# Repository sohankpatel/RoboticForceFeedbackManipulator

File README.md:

# RoboticForceFeedbackManipulator
Final Project for ECE 445, Manipulator with user force-feedback

This is a project I did for my Senior Design class

It is a Robotic manipulator and glove system meant to allow the wearer to "feel" forces from the robotic hand

Details are contained in the Final Paper

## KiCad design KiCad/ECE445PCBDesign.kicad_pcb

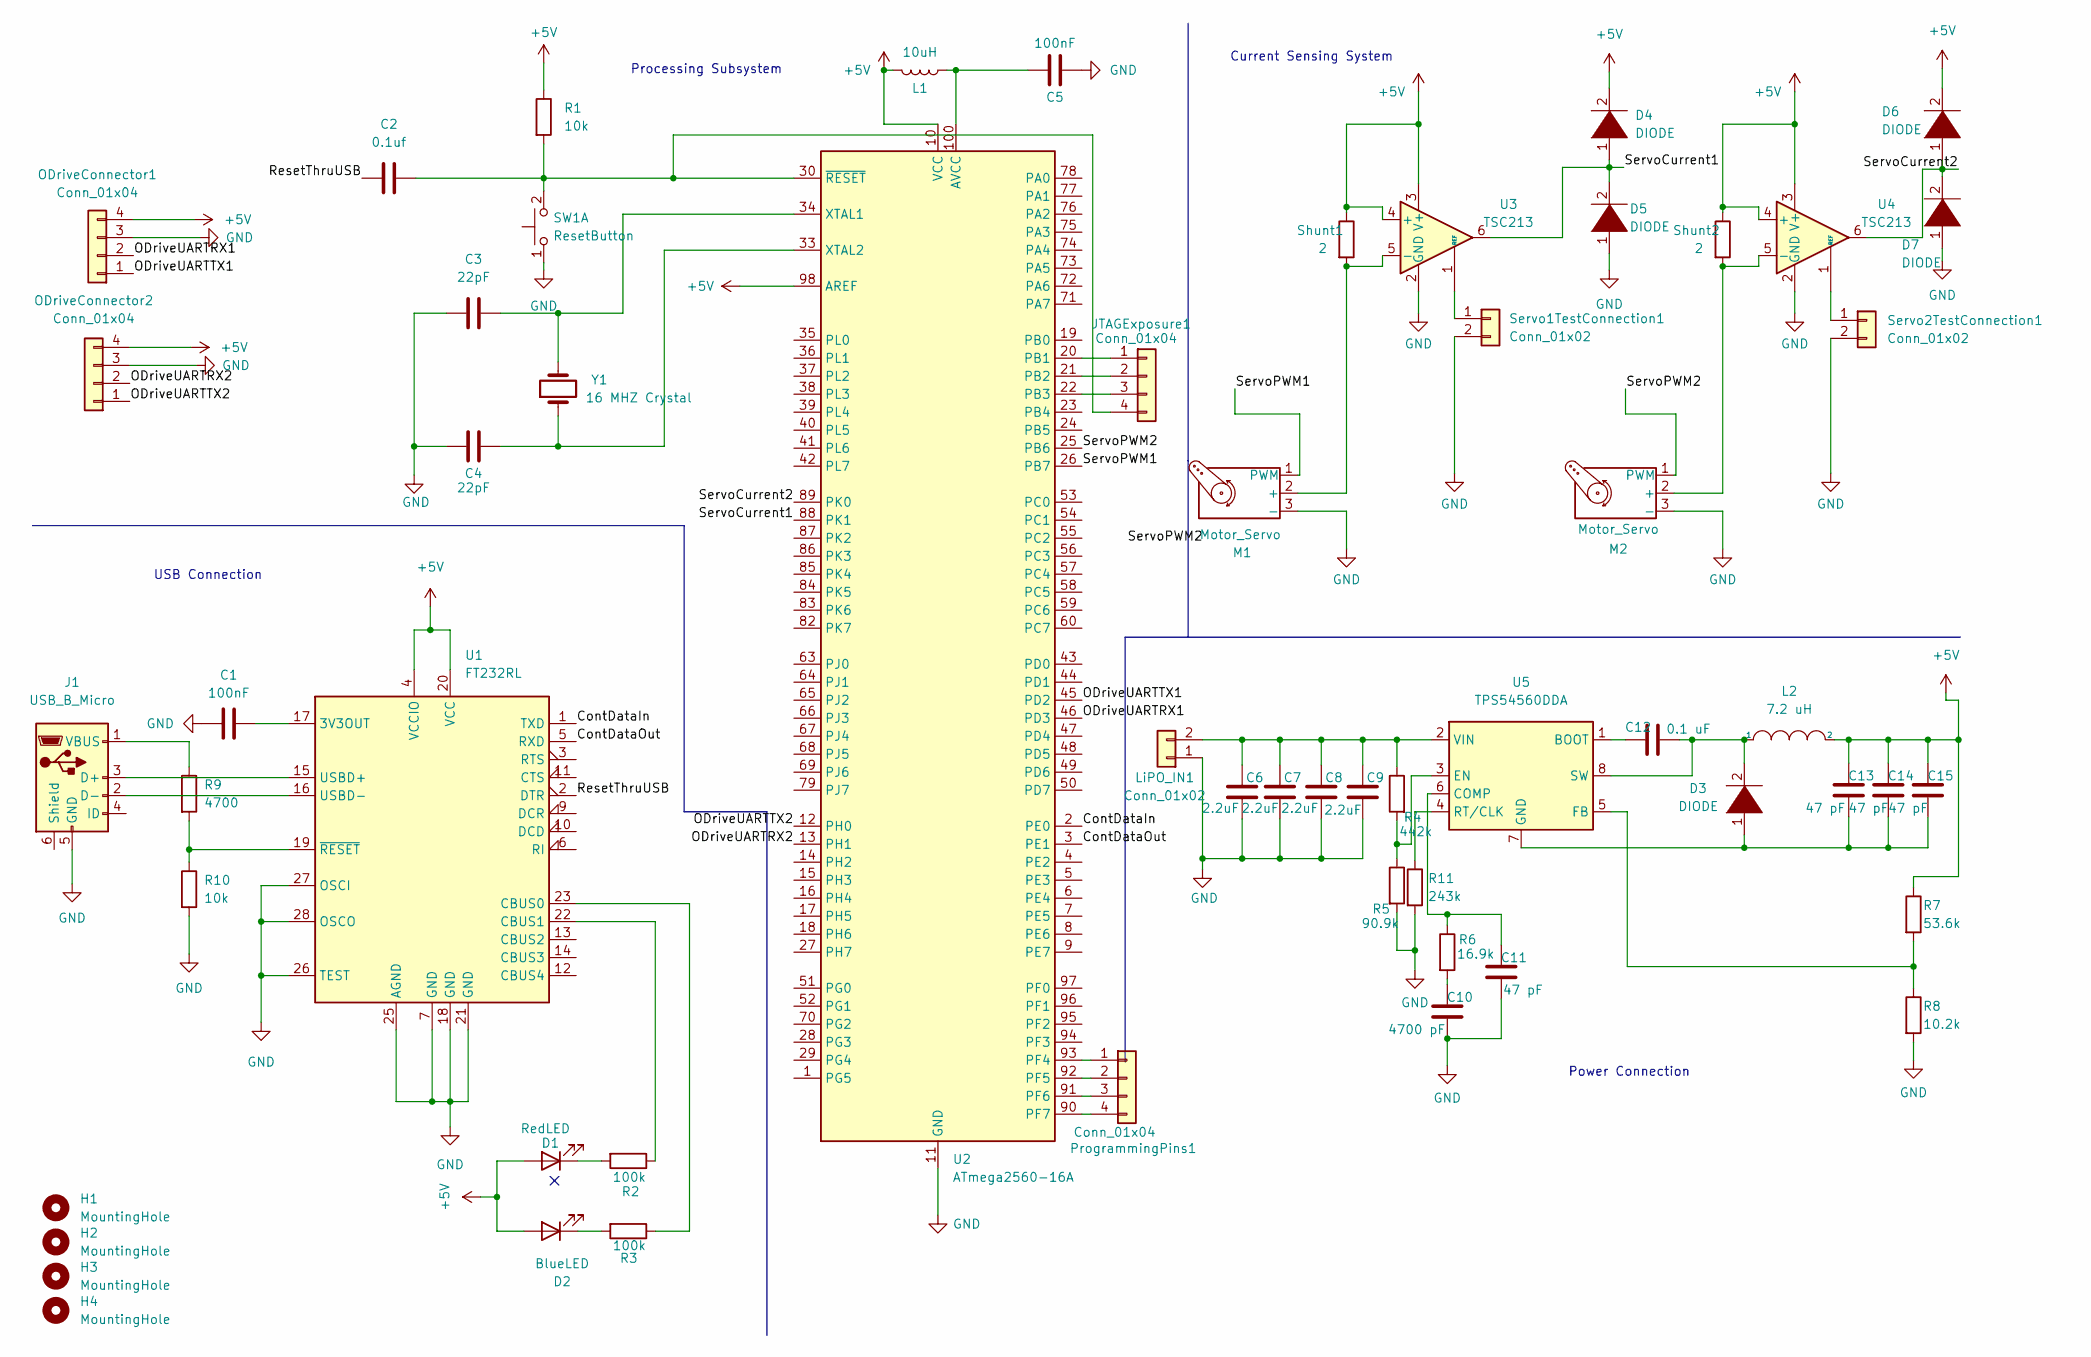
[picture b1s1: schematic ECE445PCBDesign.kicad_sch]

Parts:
C1, C5: 100nF; C_0805_2012Metric_Pad1.18x1.45mm_HandSolder
C2: 0.1uf; C_0805_2012Metric_Pad1.18x1.45mm_HandSolder
C3, C4: 22pF; C_0805_2012Metric_Pad1.18x1.45mm_HandSolder
C6, C7, C8, C9: 2.2uF; C_0805_2012Metric_Pad1.18x1.45mm_HandSolder
C10: 4700 pF; C_0805_2012Metric_Pad1.18x1.45mm_HandSolder
C11, C13, C14, C15: 47 pF; C_0805_2012Metric_Pad1.18x1.45mm_HandSolder
C12: 0.1 uF; C_0805_2012Metric_Pad1.18x1.45mm_HandSolder
D1: RedLED; D_0603_1608Metric_Pad1.05x0.95mm_HandSolder
D2: BlueLED; D_0603_1608Metric_Pad1.05x0.95mm_HandSolder
D3, D4, D5, D6, D7: DIODE; Vishay-B360A-E3_61T-0-0-0
H1, H2, H3, H4: MountingHole; MountingHole_3.2mm_M3
J1: USB_B_Micro; USB_Mini-B_AdamTech_MUSB-B5-S-VT-TSMT-1_SMD_Vertical
JTAGExposure1: Conn_01x04; Molex_KK-254_AE-6410-04A_1x04_P2.54mm_Vertical
L1: 10uH; L_0603_1608Metric_Pad1.05x0.95mm_HandSolder
L2: 7.2 uH; WE-PDF59
LiPO_IN1: Conn_01x02; SolderWire-2sqmm_1x02_P7.8mm_D2mm_OD3.9mm
M1, M2: Motor_Servo; Molex_KK-254_AE-6410-03A_1x03_P2.54mm_Vertical
ODriveConnector1, ODriveConnector2: Conn_01x04; Molex_KK-254_AE-6410-04A_1x04_P2.54mm_Vertical
ProgrammingPins1: Conn_01x04; Molex_KK-254_AE-6410-04A_1x04_P2.54mm_Vertical
R1, R10: 10k; R_0805_2012Metric_Pad1.20x1.40mm_HandSolder
R2, R3: 100k; R_0805_2012Metric_Pad1.20x1.40mm_HandSolder
R4: 442k; R_0805_2012Metric_Pad1.20x1.40mm_HandSolder
R5: 90.9k; R_0805_2012Metric_Pad1.20x1.40mm_HandSolder
R6: 16.9k; R_0805_2012Metric_Pad1.20x1.40mm_HandSolder
R7: 53.6k; R_0805_2012Metric_Pad1.20x1.40mm_HandSolder
R8: 10.2k; R_0805_2012Metric_Pad1.20x1.40mm_HandSolder
R9: 4700; R_0805_2012Metric_Pad1.20x1.40mm_HandSolder
R11: 243k; R_0805_2012Metric_Pad1.20x1.40mm_HandSolder
SW1: ResetButton; SW_Push_1P1T_NO_6x6mm_H9.5mm
Servo1TestConnection1, Servo2TestConnection1: Conn_01x02; Molex_KK-254_AE-6410-02A_1x02_P2.54mm_Vertical
Shunt1, Shunt2: 2; R_0805_2012Metric_Pad1.20x1.40mm_HandSolder
U1: FT232RL; SSOP-28_5.3x10.2mm_P0.65mm
U2: ATmega2560-16A; TQFP-100_14x14mm_P0.5mm
U3, U4: TSC213; TSC213ICT
U5: TPS54560DDA; Texas_R-PDSO-G8_EP2.95x4.9mm_Mask2.4x3.1mm_ThermalVias
Y1: 16 MHZ Crystal; 830058383B

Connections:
+5V: C13.2, C14.2, C15.2, D1.2 (A), D2.2 (A), D4.2 (A), D6.2 (A), L1.2, L2.2, ODriveConnector1.4, ODriveConnector2.4, R1.1, R7.1, Shunt1.1, Shunt2.1, U1.4 (VCCIO), U1.20 (VCC), U2.10 (VCC), U2.31 (VCC), U2.61 (VCC), U2.80 (VCC), U2.98 (AREF), U3.3 (V+), U3.4 (+), U4.3 (V+), U4.4 (+)
/ContDataIn: U1.1 (TXD), U2.2 (PE0)
/ContDataOut: U1.5 (RXD), U2.3 (PE1)
/ODriveUARTRX1: ODriveConnector1.2, U2.46 (PD3)
/ODriveUARTRX2: ODriveConnector2.2, U2.13 (PH1)
/ODriveUARTTX1: ODriveConnector1.1, U2.45 (PD2)
/ODriveUARTTX2: ODriveConnector2.1, U2.12 (PH0)
/ResetThruUSB: C2.1, U1.2 (DTR)
/ServoCurrent1: D4.1 (K), D5.2 (A), U2.88 (PK1), U3.6
/ServoCurrent2: D6.1 (K), D7.2 (A), U2.89 (PK0), U4.6
/ServoPWM1: M1.1 (PWM), U2.26 (PB7)
/ServoPWM2: M2.1 (PWM), U2.25 (PB6)
GND: C1.1, C3.1, C4.1, C5.2, C6.1, C7.1, C8.1, C9.1, C10.1, C11.1, D5.1 (K), D7.1 (K), J1.5 (GND), LiPO_IN1.1, M1.3 (-), M2.3 (-), ODriveConnector1.3, ODriveConnector2.3, R5.2, R8.2, R10.2, R11.2, SW1.1 (C), Servo1TestConnection1.2, Servo2TestConnection1.2, U1.7 (GND), U1.18 (GND), U1.21 (GND), U1.25 (AGND), U1.26 (TEST), U1.27 (OSCI), U1.28 (OSCO), U2.11 (GND), U2.32 (GND), U2.62 (GND), U2.81 (GND), U2.99 (GND), U3.2 (GND), U4.2 (GND)
unnamed: C1.2, U1.17 (3V3OUT)
unnamed: C2.2, JTAGExposure1.4, R1.2, SW1.2 (D), U2.30 (~RESET)
unnamed: C3.2, U2.34 (XTAL1), Y1.2
unnamed: C4.2, U2.33 (XTAL2), Y1.1
unnamed: C5.1, L1.1, U2.100 (AVCC)
unnamed: C6.2, C7.2, C8.2, C9.2, LiPO_IN1.2, R4.1, U5.2 (VIN)
unnamed: C10.2, R6.2
unnamed: C11.2, R6.1, U5.6 (COMP)
unnamed: C12.1, D3.2 (A), L2.1, U5.8 (SW)
unnamed: C12.2, U5.1 (BOOT)
unnamed: C13.1, C14.1, C15.1, D3.1 (K), U5.7 (GND), U5.9 (GND)
unnamed: D1.1 (K), R2.2
unnamed: D2.1 (K), R3.2
unnamed: M1.2 (+), Shunt1.2, U3.5 (-)
unnamed: M2.2 (+), Shunt2.2, U4.5 (-)
unnamed: R2.1, U1.22 (CBUS1)
unnamed: R3.1, U1.23 (CBUS0)
unnamed: R4.2, R5.1, U5.3 (EN)
unnamed: R7.2, R8.1, U5.5 (FB)
unnamed: J1.1 (VBUS), R9.1
unnamed: Servo1TestConnection1.1, U3.1 (REF)
unnamed: Servo2TestConnection1.1, U4.1 (REF)
unnamed: J1.3 (D+), U1.15 (USBD+)
unnamed: J1.2 (D-), U1.16 (USBD-)
unnamed: R9.2, R10.1, U1.19 (~RESET)
unnamed: JTAGExposure1.1, U2.20 (PB1)
unnamed: JTAGExposure1.2, U2.21 (PB2)
unnamed: JTAGExposure1.3, U2.22 (PB3)
unnamed: ProgrammingPins1.4, U2.90 (PF7)
unnamed: ProgrammingPins1.3, U2.91 (PF6)
unnamed: ProgrammingPins1.2, U2.92 (PF5)
unnamed: ProgrammingPins1.1, U2.93 (PF4)
unnamed: R11.1, U5.4 (RT/CLK)

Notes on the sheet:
Processing Subsystem
Power Connection
USB Connection
Current Sensing System

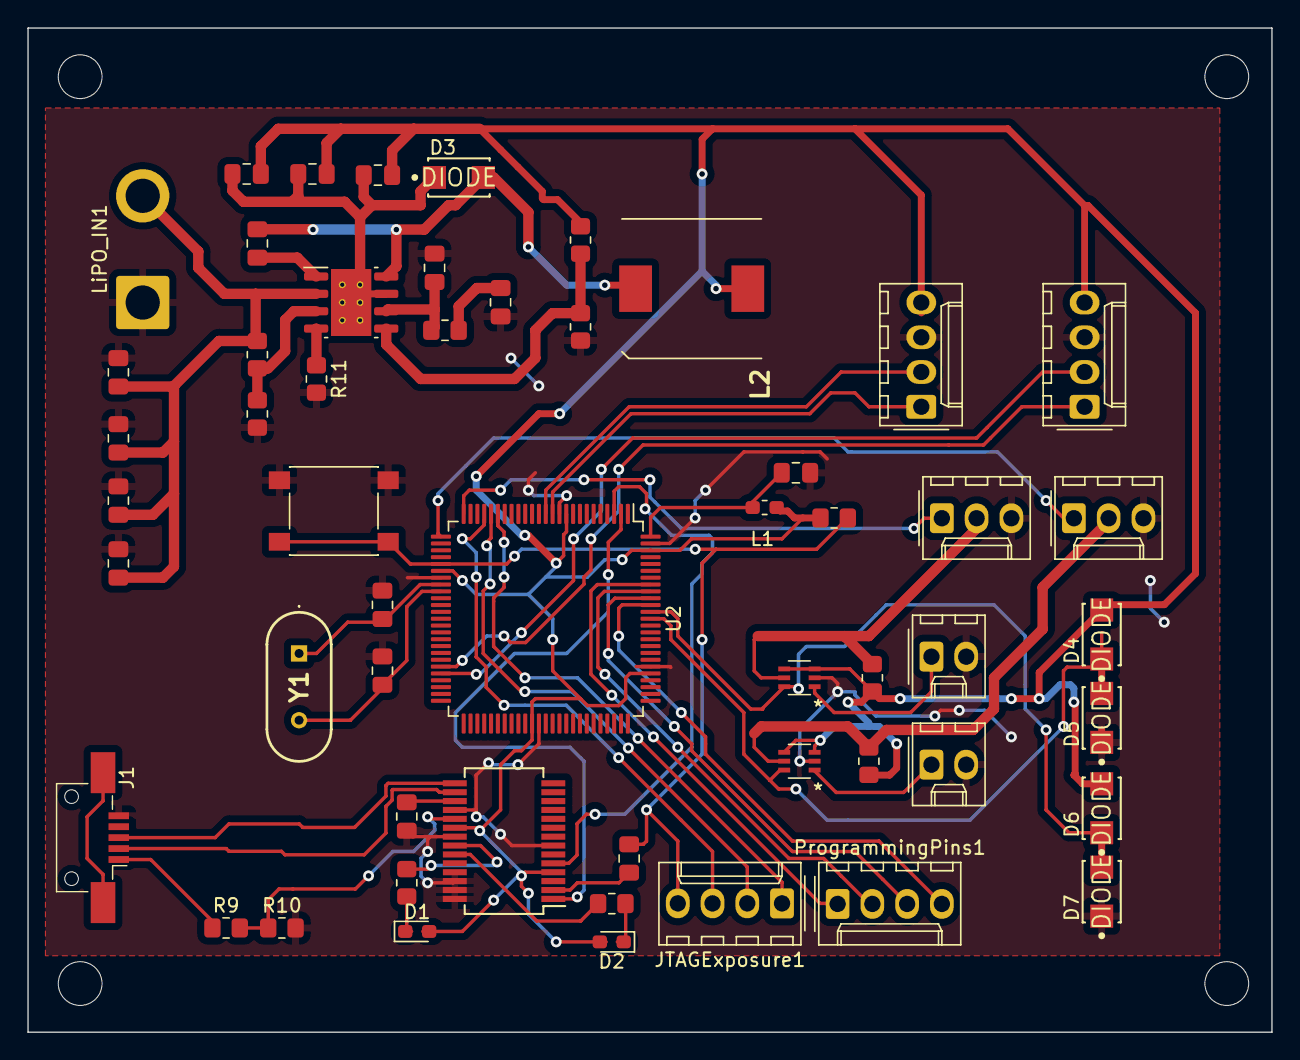
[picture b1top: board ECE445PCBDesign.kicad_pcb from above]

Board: 2 copper layers, 90.9 x 73.4 mm, 58 parts (0 on the bottom side), 46 nets.

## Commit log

2022-12-08 Adding CAD, programs and library
2022-12-08 Added remaining manipulator CAD and PCB design

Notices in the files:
parts and their libraries:
Copyright 2021 Accelerated Designs. All rights reserved.
